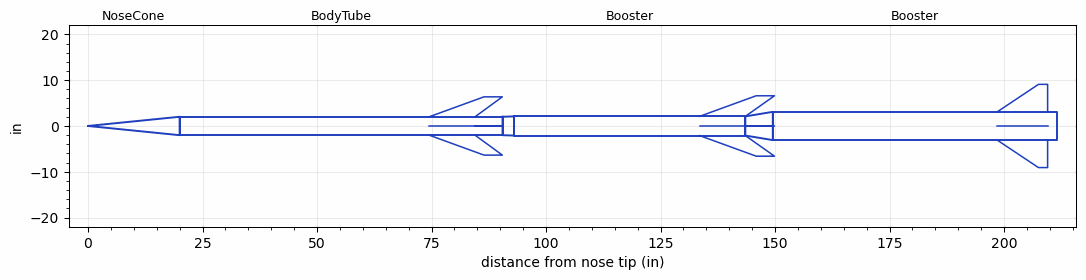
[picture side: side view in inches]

<RASAeroDocument>
 <FileVersion>2</FileVersion>
 <RocketDesign>
  <NoseCone>
   <Length>20</Length>
   <Diameter>4.02</Diameter>
   <Shape>Conical</Shape>
   <BluntRadius>0.0675</BluntRadius>
   <Location>0</Location>
  </NoseCone>
  <BodyTube>
   <Length>70.5</Length>
   <Diameter>4.02</Diameter>
   <Location>20</Location>
   <Fin>
    <Count>4</Count>
    <Chord>10</Chord>
    <Span>4.35</Span>
    <SweepDistance>11.952</SweepDistance>
    <TipChord>4</TipChord>
    <Thickness>0.25</Thickness>
    <LERadius>0.03</LERadius>
    <Location>16</Location>
    <AirfoilSection>Hexagonal</AirfoilSection>
    <FX1>2</FX1>
    <FX3>2</FX3>
   </Fin>
  </BodyTube>
  <Booster>
   <Length>50.5</Length>
   <Diameter>4.182</Diameter>
   <InsideDiameter>4.02</InsideDiameter>
   <Location>90.5</Location>
   <ShoulderLength>2.5</ShoulderLength>
   <Fin>
    <Count>4</Count>
    <Chord>10</Chord>
    <Span>4.5</Span>
    <SweepDistance>12.364</SweepDistance>
    <TipChord>4</TipChord>
    <Thickness>0.25</Thickness>
    <LERadius>0.03</LERadius>
    <Location>10</Location>
    <AirfoilSection>Hexagonal</AirfoilSection>
    <FX1>2</FX1>
    <FX3>2</FX3>
   </Fin>
  </Booster>
  <Booster>
   <Length>62</Length>
   <Diameter>6.17</Diameter>
   <InsideDiameter>4.182</InsideDiameter>
   <Location>143.5</Location>
   <ShoulderLength>6</ShoulderLength>
   <Fin>
    <Count>4</Count>
    <Chord>11</Chord>
    <Span>6</Span>
    <SweepDistance>9</SweepDistance>
    <TipChord>2</TipChord>
    <Thickness>0.25</Thickness>
    <LERadius>0.03</LERadius>
    <Location>13</Location>
    <AirfoilSection>Hexagonal</AirfoilSection>
    <FX1>2</FX1>
    <FX3>2</FX3>
   </Fin>
  </Booster>
  <Surface>Rough Camouflage Paint</Surface>
  <ModifiedBarrowman>False</ModifiedBarrowman>
  <Turbulence>True</Turbulence>
  <UseBooster1>False</UseBooster1>
  <UseBooster2>False</UseBooster2>
 </RocketDesign>
 <LaunchSite>
  <Altitude>2000</Altitude>
  <Pressure>0</Pressure>
  <RodAngle>3</RodAngle>
  <RodLength>20</RodLength>
  <Temperature>74</Temperature>
  <WindSpeed>5</WindSpeed>
 </LaunchSite>
 <Recovery>
  <Altitude1>1000</Altitude1>
  <Altitude2>1000</Altitude2>
  <DeviceType1>Parachute</DeviceType1>
  <DeviceType2>Parachute</DeviceType2>
  <Event1>True</Event1>
  <Event2>True</Event2>
  <Size1>12</Size1>
  <Size2>48</Size2>
  <EventType1>Apogee</EventType1>
  <EventType2>Altitude</EventType2>
  <CD1>0.97</CD1>
  <CD2>2.2</CD2>
 </Recovery>
 <SimulationList>
  <Simulation>
   <SustainerEngine>N5800-CS  (CTI)</SustainerEngine>
   <SustainerLaunchWt>48.1</SustainerLaunchWt>
   <SustainerNozzleDiameter>2.5</SustainerNozzleDiameter>
   <SustainerCG>56.29</SustainerCG>
   <SustainerIgnitionDelay>7</SustainerIgnitionDelay>
   <Booster1Engine>O3400-IM-P  (CTI)</Booster1Engine>
   <Booster1LaunchWt>96.4</Booster1LaunchWt>
   <Booster1SeparationDelay>0</Booster1SeparationDelay>
   <Booster1IgnitionDelay>7</Booster1IgnitionDelay>
   <Booster1CG>92.5</Booster1CG>
   <Booster1NozzleDiameter>2.5</Booster1NozzleDiameter>
   <IncludeBooster1>True</IncludeBooster1>
   <Booster2Engine>O6000W-P  (AeroTech)</Booster2Engine>
   <Booster2LaunchWt>182</Booster2LaunchWt>
   <Booster2Delay>0</Booster2Delay>
   <Booster2CG>137</Booster2CG>
   <Booster2NozzleDiameter>3</Booster2NozzleDiameter>
   <IncludeBooster2>True</IncludeBooster2>
   <TimetoApogee>196.6226</TimetoApogee>
   <MaxAltitude>497861.3</MaxAltitude>
   <MaxVelocity>5746.049</MaxVelocity>
  </Simulation>
 </SimulationList>
</RASAeroDocument>
